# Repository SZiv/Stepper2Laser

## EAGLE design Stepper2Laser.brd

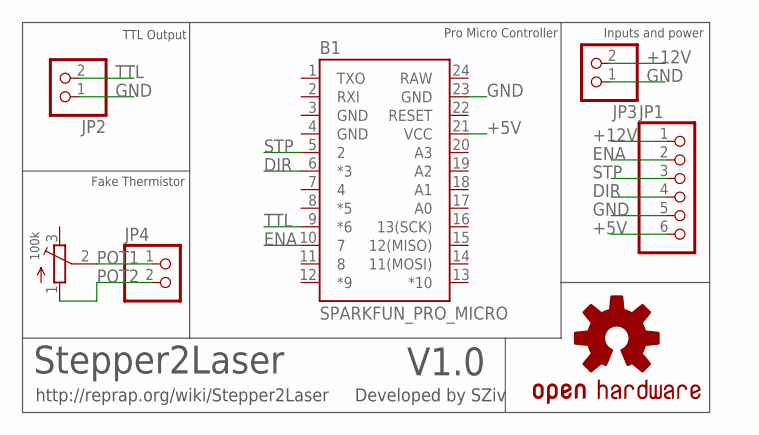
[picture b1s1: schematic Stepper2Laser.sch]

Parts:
B1: SPARKFUN_PRO_MICRO
JP1: PINHD-1X6; 1X06
JP2, JP3, JP4: PINHD-1X2; 1X02
LOGO1: OSHW-LOGOMINI; OSHW-LOGO-MINI
TM1: TRIMPOT3386; TRIM-3386

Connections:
+5V: B1.21 (VCC), JP1.6
+12V: JP1.1, JP3.2
DIR: B1.6 (*3), JP1.4
ENA: B1.10 (7), JP1.2
GND: B1.3 (GND), B1.4 (GND), B1.23 (GND), JP1.5, JP2.1, JP3.1
POT1: JP4.1, TM1.2 (S)
POT2: JP4.2, TM1.1 (A)
RAW: B1.24 (RAW)
STP: B1.5 (2), JP1.3
TTL: B1.9 (*6), JP2.2

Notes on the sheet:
Developed by SZiv
http://reprap.org/wiki/Stepper2Laser
Stepper2Laser
V1.0
Inputs and power
TTL Output
Pro Micro Controller
Fake Thermistor
100k

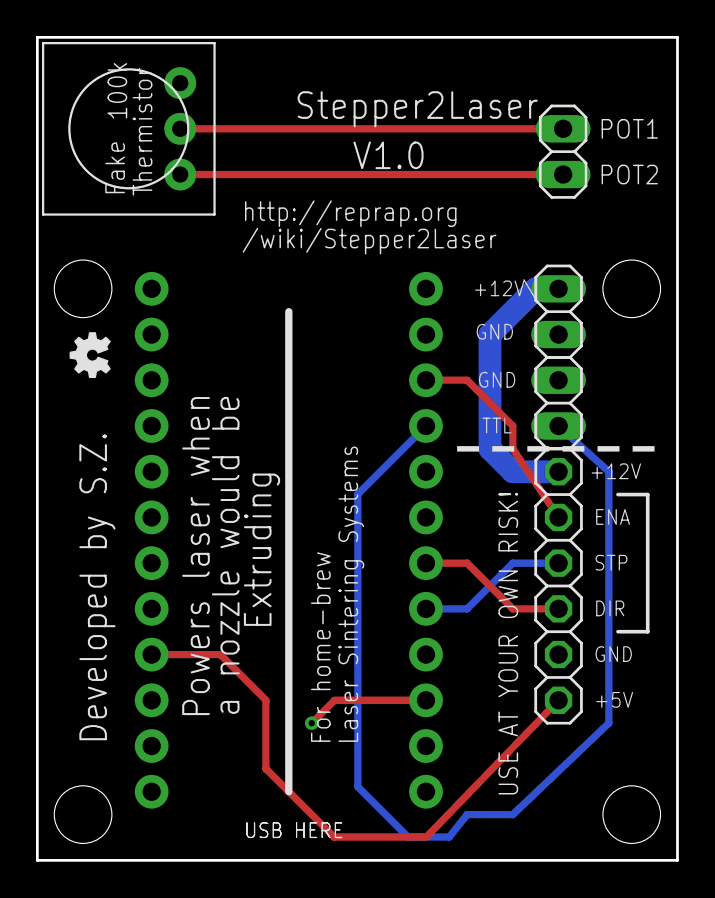
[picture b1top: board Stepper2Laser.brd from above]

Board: 2 copper layers, 35.6 x 45.7 mm, 7 parts (0 on the bottom side), 9 nets.

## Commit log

2017-09-25 :confetti_ball: Added .gitattributes & .gitignore files
2017-09-25 Main Commit
    First Commit
2017-11-19 Added first firmware version, fixed some trace issues.
    Added firmware and minor fixes. Still in development, and relies on
    retraction to work.

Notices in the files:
parts and their libraries:
SparkFun-Boards: Licensing: Creative Commons ShareAlike 4.0 International - https://creativecommons.org/licenses/by-sa/4.0
